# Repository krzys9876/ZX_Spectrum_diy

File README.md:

# ZX_Spectrum_diy

All boards that I designed, etched and soldered to create a full-diy replica of ZX Spectrum.
**Kicad4** (just a keyboard) and **Kicad5**

This is NOT a cycle-perfect replica so do not expect to launch fancy demos on it. 
The project started as a breadboard simplest possible computer using Z80. Quite quickly I started thinking of making a replica of ZX Spectrum - the first computer I ever used as a kid. All I wanted was to:

- launch Knight Lore - the best game ever
- write some Basic programs - to feel the magic of programming again - and I did!

Have questions? Just drop me an email.

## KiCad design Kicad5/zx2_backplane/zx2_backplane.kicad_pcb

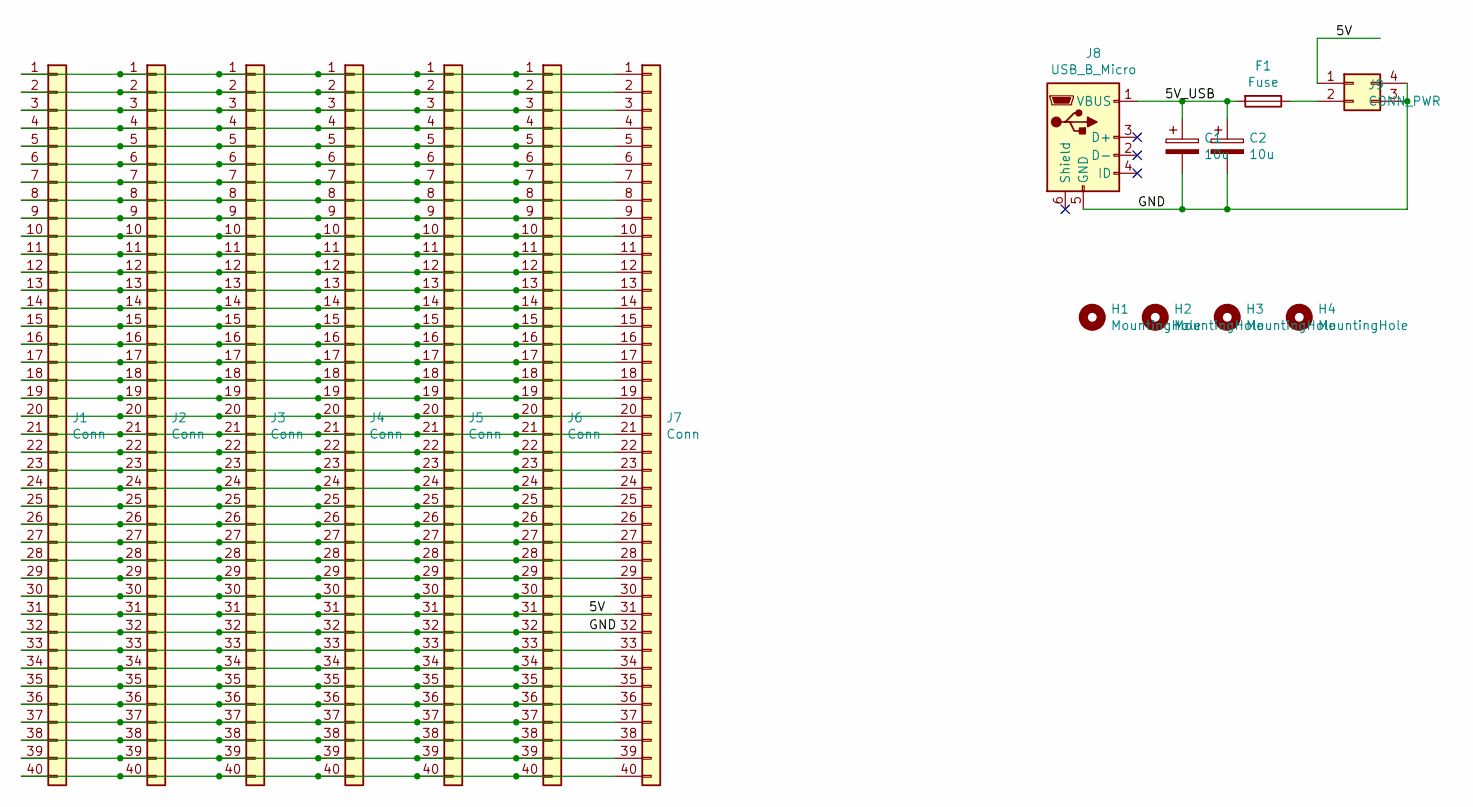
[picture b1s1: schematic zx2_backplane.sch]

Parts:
C1, C2: 10u; C_1210_3225Metric
F1: Fuse; Fuse_1812_4532Metric
H1, H2, H3, H4: MountingHole; MountingHole_3.2mm_M3
J1, J2, J3, J4, J5, J6, J7: Conn; PinHeader_1x40_P2.54mm_Vertical
J8: USB_B_Micro; USB_Micro-B_Amphenol_10104110_Horizontal
J9: CONN_PWR; PinHeader_2x02_P2.54mm_Vertical

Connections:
/5V: J1.31, J2.31, J3.31, J4.31, J5.31, J6.31, J7.31, J9.1
/5V_USB: C1.1, C2.1, F1.2, J8.1 (VBUS)
/GND: C1.2, C2.2, J1.32, J2.32, J3.32, J4.32, J5.32, J6.32, J7.32, J8.5 (GND), J9.3, J9.4
unnamed: F1.1, J9.2
unnamed: J1.1, J2.1, J3.1, J4.1, J5.1, J6.1, J7.1
unnamed: J1.2, J2.2, J3.2, J4.2, J5.2, J6.2, J7.2
unnamed: J1.3, J2.3, J3.3, J4.3, J5.3, J6.3, J7.3
unnamed: J1.4, J2.4, J3.4, J4.4, J5.4, J6.4, J7.4
unnamed: J1.5, J2.5, J3.5, J4.5, J5.5, J6.5, J7.5
unnamed: J1.6, J2.6, J3.6, J4.6, J5.6, J6.6, J7.6
unnamed: J1.7, J2.7, J3.7, J4.7, J5.7, J6.7, J7.7
unnamed: J1.8, J2.8, J3.8, J4.8, J5.8, J6.8, J7.8
unnamed: J1.9, J2.9, J3.9, J4.9, J5.9, J6.9, J7.9
unnamed: J1.10, J2.10, J3.10, J4.10, J5.10, J6.10, J7.10
unnamed: J1.11, J2.11, J3.11, J4.11, J5.11, J6.11, J7.11
unnamed: J1.12, J2.12, J3.12, J4.12, J5.12, J6.12, J7.12
unnamed: J1.13, J2.13, J3.13, J4.13, J5.13, J6.13, J7.13
unnamed: J1.14, J2.14, J3.14, J4.14, J5.14, J6.14, J7.14
unnamed: J1.15, J2.15, J3.15, J4.15, J5.15, J6.15, J7.15
unnamed: J1.16, J2.16, J3.16, J4.16, J5.16, J6.16, J7.16
unnamed: J1.17, J2.17, J3.17, J4.17, J5.17, J6.17, J7.17
unnamed: J1.18, J2.18, J3.18, J4.18, J5.18, J6.18, J7.18
unnamed: J1.19, J2.19, J3.19, J4.19, J5.19, J6.19, J7.19
unnamed: J1.20, J2.20, J3.20, J4.20, J5.20, J6.20, J7.20
unnamed: J1.21, J2.21, J3.21, J4.21, J5.21, J6.21, J7.21
unnamed: J1.22, J2.22, J3.22, J4.22, J5.22, J6.22, J7.22
unnamed: J1.23, J2.23, J3.23, J4.23, J5.23, J6.23, J7.23
unnamed: J1.24, J2.24, J3.24, J4.24, J5.24, J6.24, J7.24
unnamed: J1.25, J2.25, J3.25, J4.25, J5.25, J6.25, J7.25
unnamed: J1.26, J2.26, J3.26, J4.26, J5.26, J6.26, J7.26
unnamed: J1.27, J2.27, J3.27, J4.27, J5.27, J6.27, J7.27
unnamed: J1.28, J2.28, J3.28, J4.28, J5.28, J6.28, J7.28
unnamed: J1.29, J2.29, J3.29, J4.29, J5.29, J6.29, J7.29
unnamed: J1.30, J2.30, J3.30, J4.30, J5.30, J6.30, J7.30
unnamed: J1.33, J2.33, J3.33, J4.33, J5.33, J6.33, J7.33
unnamed: J1.34, J2.34, J3.34, J4.34, J5.34, J6.34, J7.34
unnamed: J1.35, J2.35, J3.35, J4.35, J5.35, J6.35, J7.35
unnamed: J1.36, J2.36, J3.36, J4.36, J5.36, J6.36, J7.36
unnamed: J1.37, J2.37, J3.37, J4.37, J5.37, J6.37, J7.37
unnamed: J1.38, J2.38, J3.38, J4.38, J5.38, J6.38, J7.38
unnamed: J1.39, J2.39, J3.39, J4.39, J5.39, J6.39, J7.39
unnamed: J1.40, J2.40, J3.40, J4.40, J5.40, J6.40, J7.40

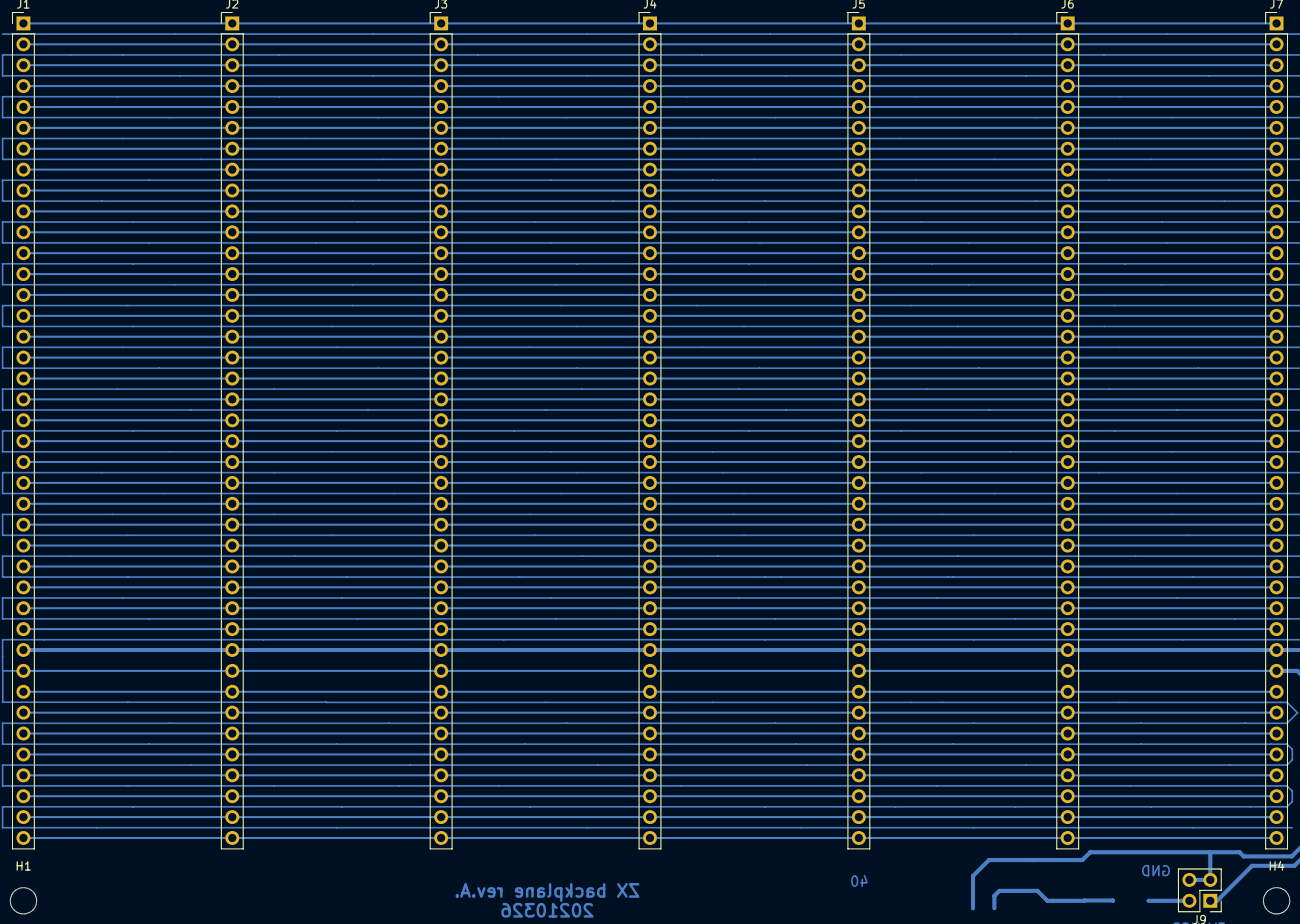
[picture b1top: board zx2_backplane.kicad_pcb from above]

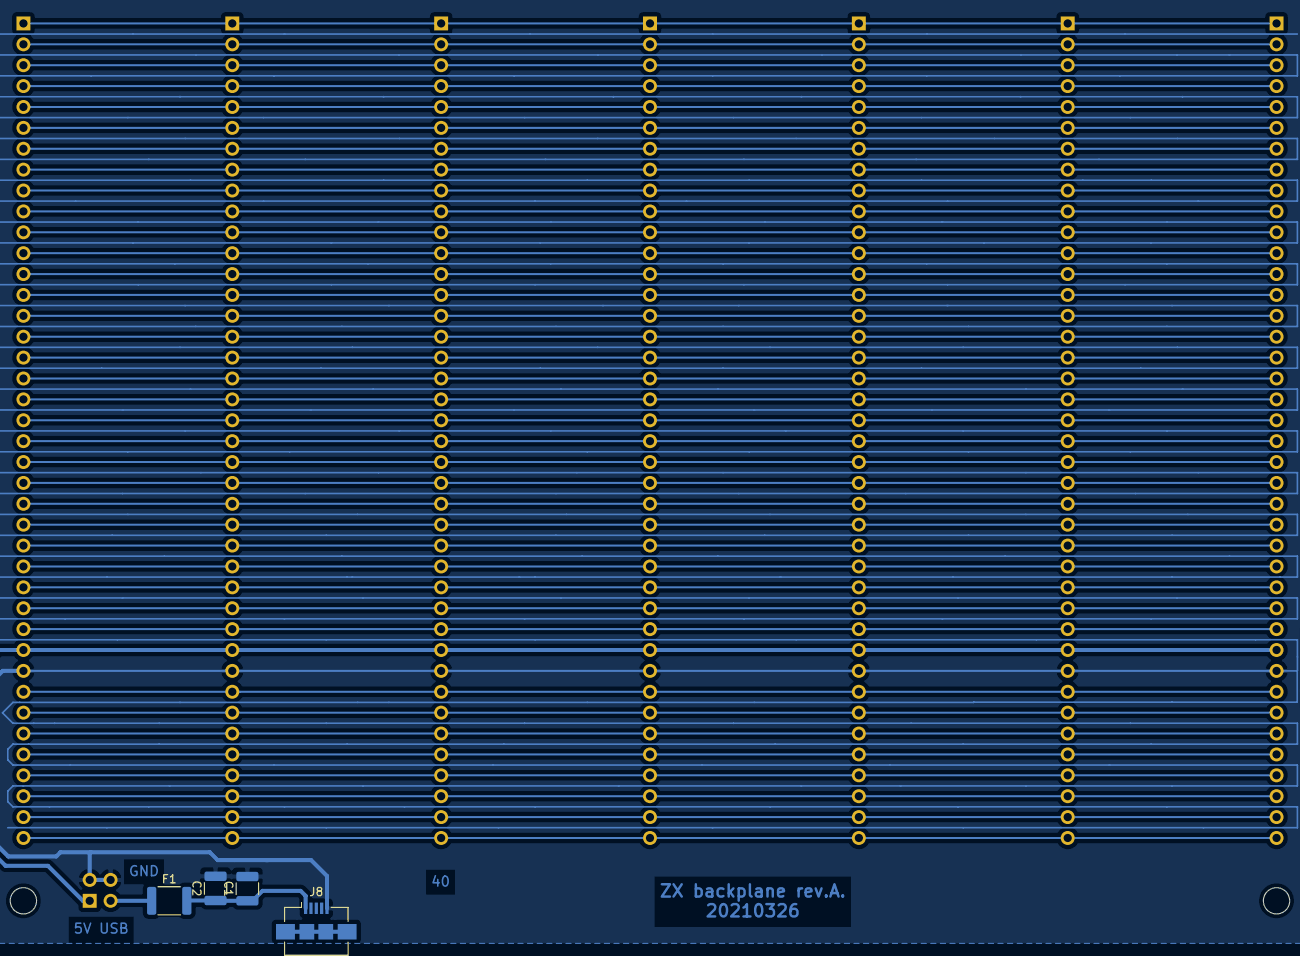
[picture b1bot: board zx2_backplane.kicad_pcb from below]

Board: 2 copper layers, 16 parts (4 on the bottom side), 42 nets.

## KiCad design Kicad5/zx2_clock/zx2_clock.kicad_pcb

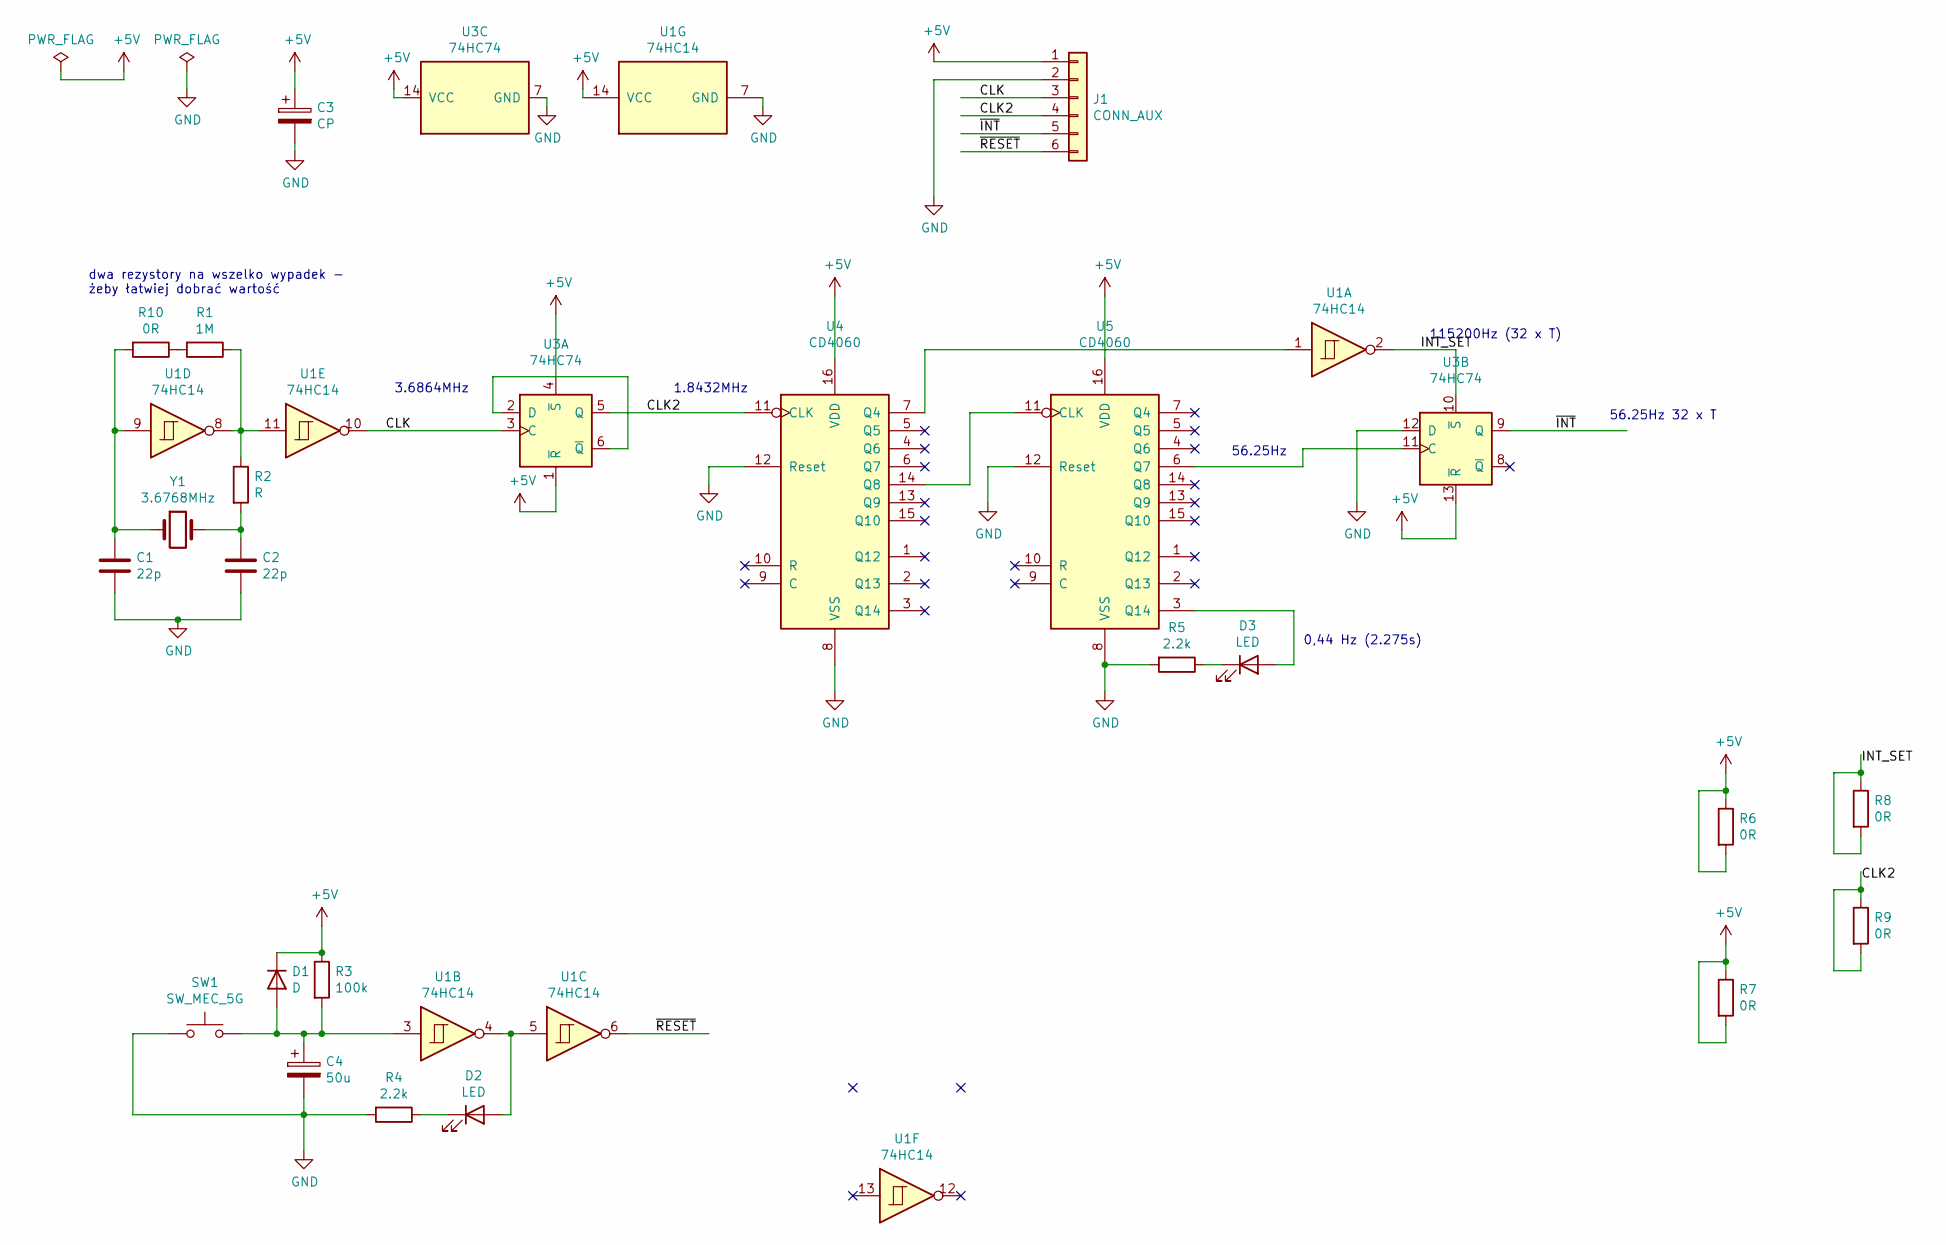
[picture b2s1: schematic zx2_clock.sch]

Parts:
C1, C2: 22p; C_0603_1608Metric
C3: CP; C_1210_3225Metric
C4: 50u; CP_Elec_5x3
D1: D; C_0805_2012Metric
D2, D3: LED; C_0805_2012Metric
J1: CONN_AUX; PinHeader_1x06_P2.54mm_Horizontal
R1: 1M; C_0805_2012Metric
R2: R; C_0805_2012Metric
R3: 100k; C_0805_2012Metric
R4, R5: 2.2k; C_0805_2012Metric
R6, R7, R8, R9: 0R; R_1206_3216Metric
R10: 0R; C_0805_2012Metric
SW1: SW_MEC_5G; SW_SPST_EVQPE1
U1: 74HC14; DIP-14_W7.62mm
U3: 74HC74; DIP-14_W7.62mm
U4, U5: CD4060; DIP-16_W7.62mm
Y1: 3.6768MHz; Crystal_SMD_HC49-SD

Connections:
+5V: C3.1, D1.1 (K), J1.1, R3.1, R6.1, R6.2, R7.1, R7.2, U1.14 (VCC), U3.1 (~R), U3.4 (~S), U3.13 (~R), U3.14 (VCC), U4.16 (VDD), U5.16 (VDD)
/CLK: J1.3, U1.10, U3.3 (C)
/CLK2: J1.4, R9.1, R9.2, U3.5 (Q), U4.11 (CLK)
/INT_SET: R8.1, R8.2, U1.2, U3.10 (~S)
/~INT: J1.5, U3.9 (Q)
/~RESET: J1.6, U1.6
GND: C1.2, C2.2, C3.2, C4.2, J1.2, R4.2, R5.2, SW1.1, U1.7 (GND), U3.7 (GND), U3.12 (D), U4.8 (VSS), U4.12 (Reset), U5.8 (VSS), U5.12 (Reset)
unnamed: C1.1, R10.2, U1.9, Y1.1
unnamed: C2.1, R2.2, Y1.2
unnamed: C4.1, D1.2 (A), R3.2, SW1.2, U1.3
unnamed: D2.1 (K), R4.1
unnamed: D2.2 (A), U1.4, U1.5
unnamed: D3.1 (K), R5.1
unnamed: D3.2 (A), U5.3 (Q14)
unnamed: R1.1, R2.1, U1.8, U1.11
unnamed: R1.2, R10.1
unnamed: U1.1, U4.7 (Q4)
unnamed: U3.2 (D), U3.6 (~Q)
unnamed: U3.11 (C), U5.6 (Q7)
unnamed: U4.14 (Q8), U5.11 (CLK)

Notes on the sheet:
56.25Hz
115200Hz (32 x T)
3.6864MHz
1.8432MHz
56.25Hz 32 x T
0,44 Hz (2.275s)
dwa rezystory na wszelko wypadek - żeby łatwiej dobrać wartość

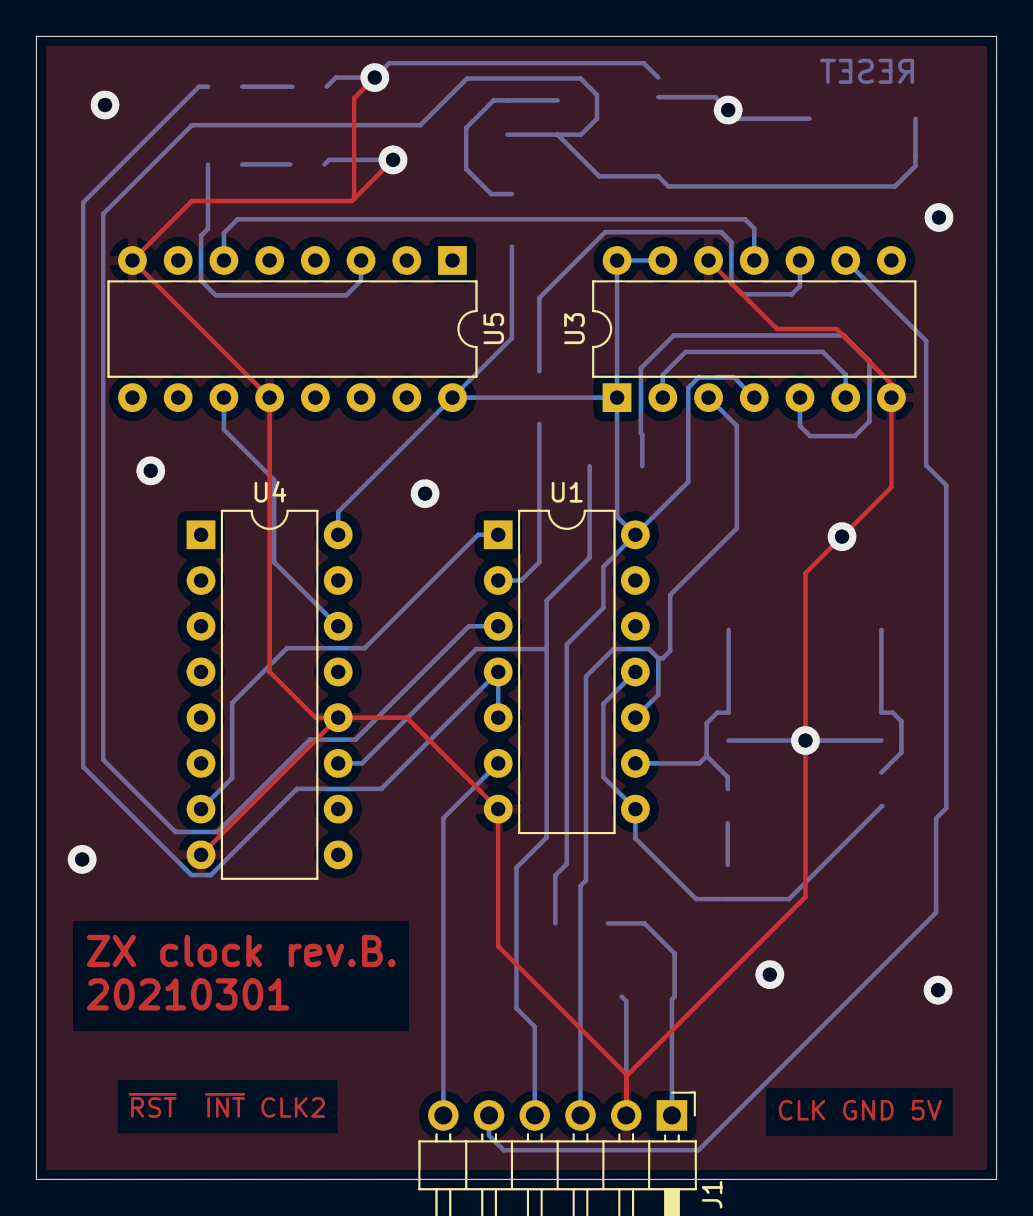
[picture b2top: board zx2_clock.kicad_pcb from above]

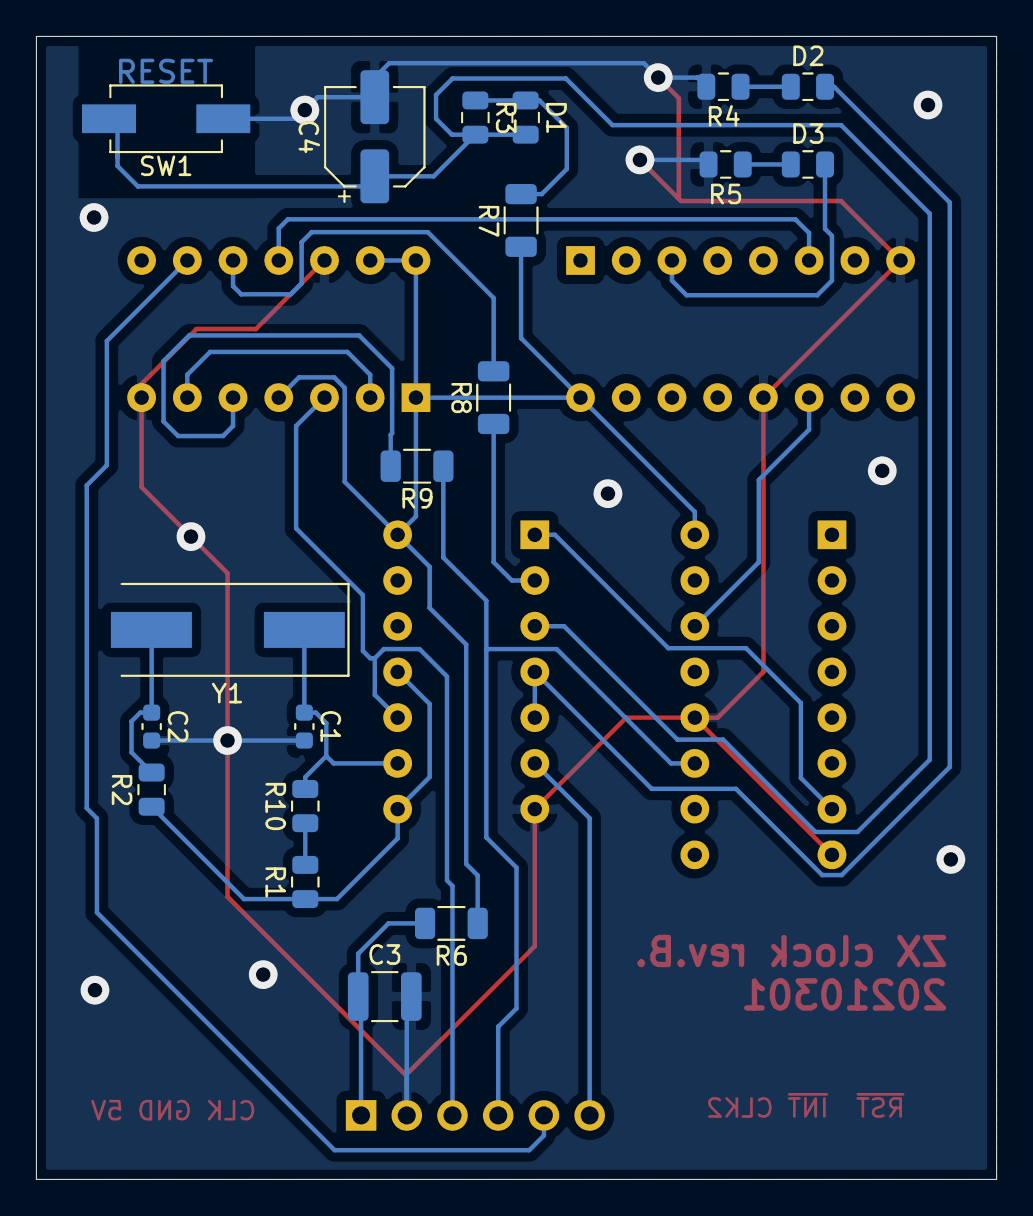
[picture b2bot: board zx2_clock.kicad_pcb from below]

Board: 2 copper layers, 53.3 x 63.5 mm, 24 parts (19 on the bottom side), 20 nets.

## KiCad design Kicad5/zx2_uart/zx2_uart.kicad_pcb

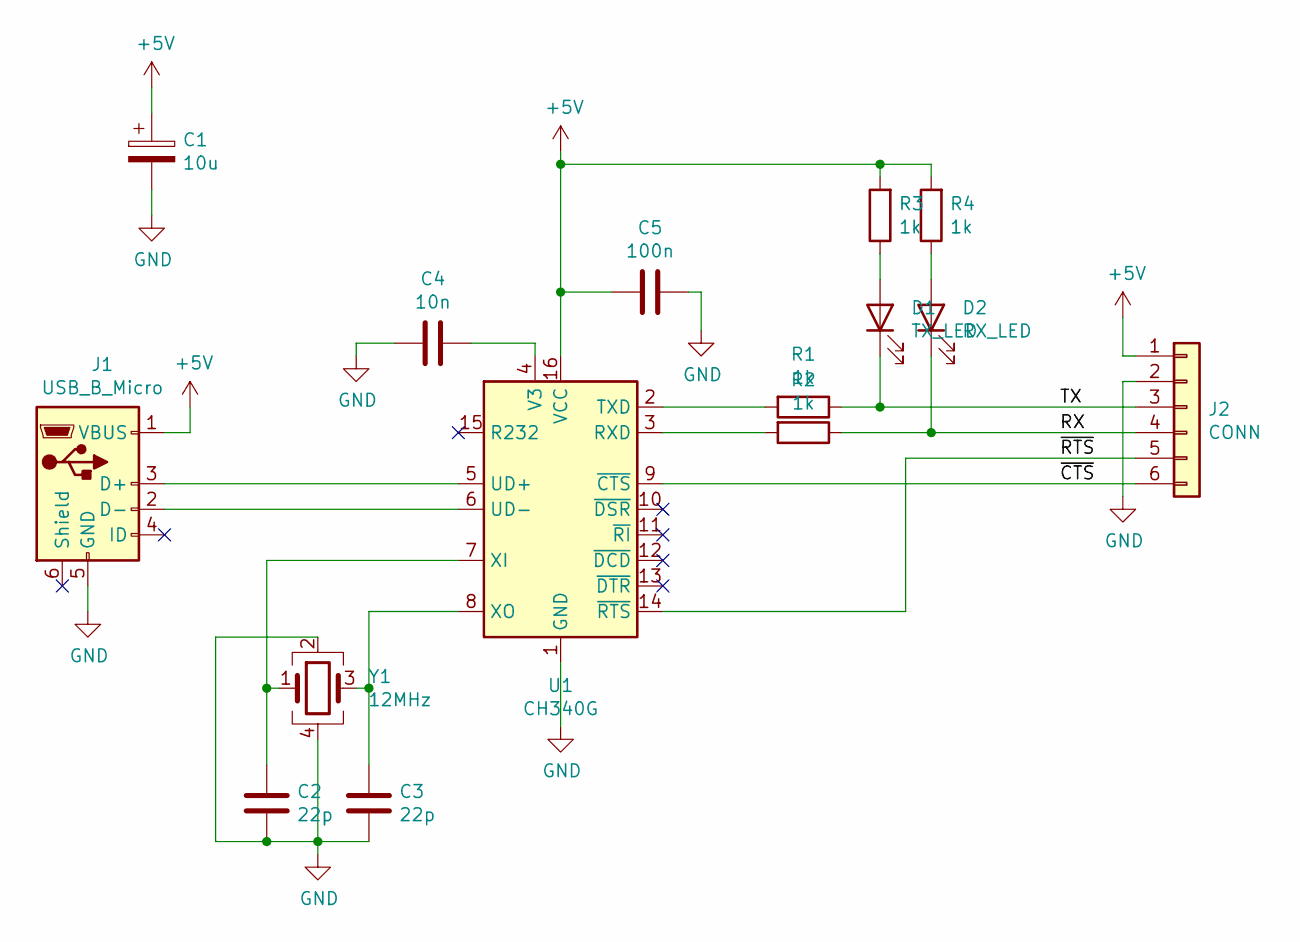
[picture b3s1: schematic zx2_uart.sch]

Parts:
C1: 10u; C_1210_3225Metric
C2, C3: 22p; C_0603_1608Metric
C4: 10n; C_1206_3216Metric
C5: 100n; C_1206_3216Metric
D1: TX_LED; D_0805_2012Metric
D2: RX_LED; D_0805_2012Metric
J1: USB_B_Micro; USB_Micro-B_Amphenol_10104110_Horizontal
J2: CONN; PinHeader_1x06_P2.54mm_Vertical
R1, R2, R3, R4: 1k; R_0805_2012Metric
U1: CH340G; SOIC-16_3.9x9.9mm_P1.27mm
Y1: 12MHz; Crystal_SMD_3225-4Pin_3.2x2.5mm

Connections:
+5V: C1.1, C5.2, J1.1 (VBUS), J2.1, R3.2, R4.2, U1.16 (VCC)
/RX: D2.1 (K), J2.4, R2.1
/TX: D1.1 (K), J2.3, R1.1
/~CTS: J2.6, U1.9 (~CTS)
/~RTS: J2.5, U1.14 (~RTS)
GND: C1.2, C2.1, C3.1, C4.2, C5.1, J1.5 (GND), J2.2, U1.1 (GND), Y1.2, Y1.4
unnamed: C2.2, U1.7 (XI), Y1.1
unnamed: C3.2, U1.8 (XO), Y1.3
unnamed: C4.1, U1.4 (V3)
unnamed: D1.2 (A), R3.1
unnamed: D2.2 (A), R4.1
unnamed: J1.2 (D-), U1.6 (UD-)
unnamed: J1.3 (D+), U1.5 (UD+)
unnamed: R1.2, U1.2 (TXD)
unnamed: R2.2, U1.3 (RXD)

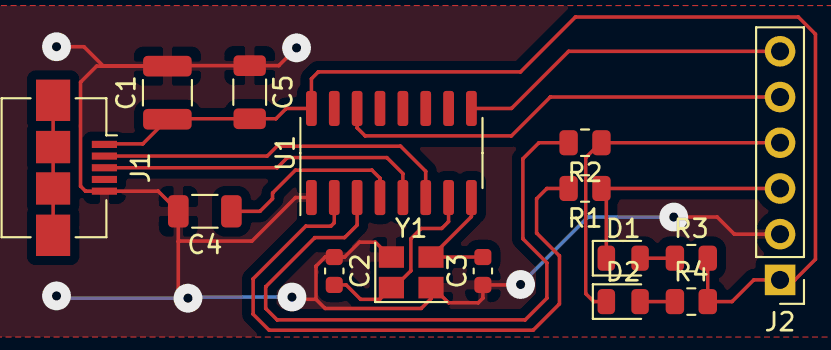
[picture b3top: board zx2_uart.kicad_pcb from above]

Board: 2 copper layers, 15 parts (0 on the bottom side), 15 nets.

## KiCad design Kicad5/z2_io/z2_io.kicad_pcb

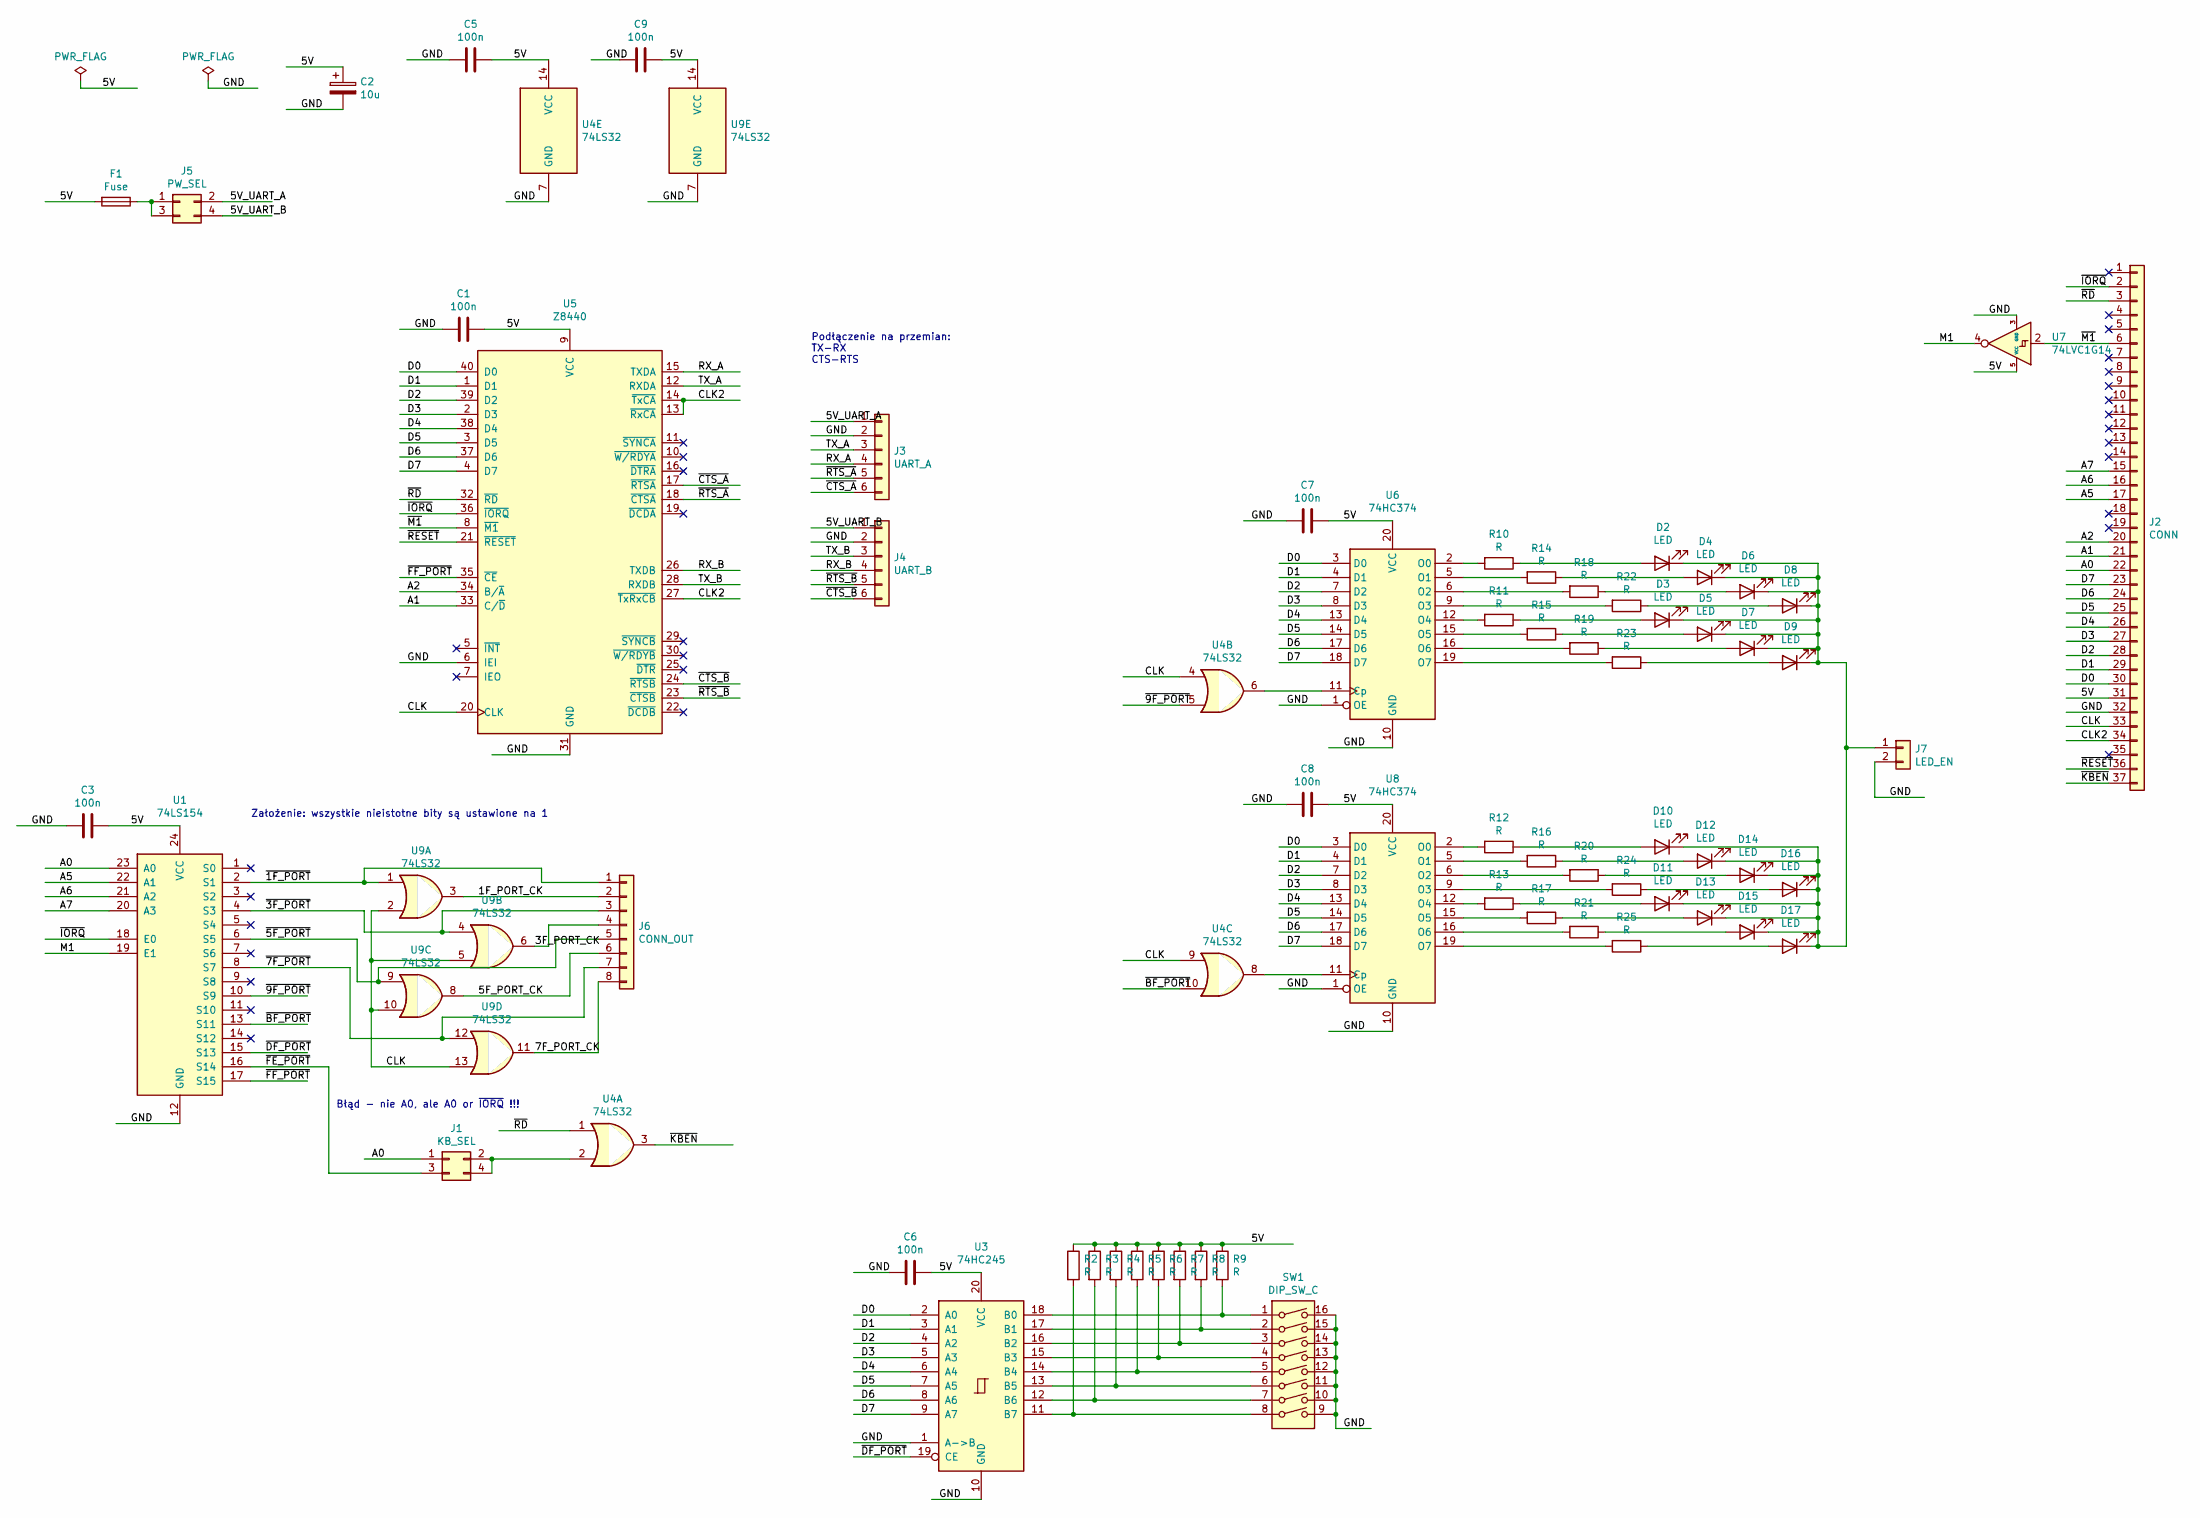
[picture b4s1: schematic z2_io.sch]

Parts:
C1, C3, C5, C6, C7, C8, C9: 100n; C_1206_3216Metric
C2: 10u; C_1210_3225Metric
D2, D3, D4, D5, D6, D7, D8, D9, D10, D11, D12, D13, D14, D15, D16, D17: LED; D_0805_2012Metric
F1: Fuse; Fuse_1812_4532Metric
J1: KB_SEL; PinHeader_2x02_P2.54mm_Vertical
J2: CONN; PinHeader_1x37_P2.54mm_Horizontal
J3: UART_A; PinHeader_1x06_P2.54mm_Horizontal
J4: UART_B; PinHeader_1x06_P2.54mm_Horizontal
J5: PW_SEL; PinHeader_2x02_P2.54mm_Vertical
J6: CONN_OUT; PinHeader_2x04_P2.54mm_Vertical
J7: LED_EN; PinHeader_1x02_P2.54mm_Vertical
R2, R3, R4, R5, R6, R7, R8, R9, R10, R11, R12, R13, R14, R15, R16, R17, R18, R19, R20, R21, R22, R23, R24, R25: R; R_0805_2012Metric
SW1: DIP_SW_C; DIP-16_W7.62mm
U1: 74LS154; DIP-24_W7.62mm
U3: 74HC245; DIP-20_W7.62mm
U4, U9: 74LS32; DIP-14_W7.62mm
U5: Z8440; DIP-40_W15.24mm
U6, U8: 74HC374; DIP-20_W7.62mm
U7: 74LVC1G14; SOT-353_SC-70-5

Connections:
/1F_PORT_CK: J6.2, U9.3
/3F_PORT_CK: J6.4, U9.6
/5F_PORT_CK: J6.6, U9.8
/5V: C1.1, C2.1, C3.1, C5.1, C6.1, C7.1, C8.1, C9.1, F1.2, J2.31, R2.1, R3.1, R4.1, R5.1, R6.1, R7.1, R8.1, R9.1, U1.24 (VCC), U3.20 (VCC), U4.14 (VCC), U5.9 (VCC), U6.20 (VCC), U7.5 (VCC), U8.20 (VCC), U9.14 (VCC)
/5V_UART_A: J3.1, J5.2
/5V_UART_B: J4.1, J5.4
/7F_PORT_CK: J6.8, U9.11
/A0: J1.1, J2.22, U1.23 (A0)
/A1: J2.21, U5.33 (C/~D)
/A2: J2.20, U5.34 (B/~A)
/A5: J2.17, U1.22 (A1)
/A6: J2.16, U1.21 (A2)
/A7: J2.15, U1.20 (A3)
/CLK: J2.33, U4.4, U4.9, U5.20 (CLK), U9.2, U9.5, U9.10, U9.13
/CLK2: J2.34, U5.13 (~RxCA), U5.14 (~TxCA), U5.27 (~TxRxCB)
/D0: J2.30, U3.2 (A0), U5.40 (D0), U6.3 (D0), U8.3 (D0)
/D1: J2.29, U3.3 (A1), U5.1 (D1), U6.4 (D1), U8.4 (D1)
/D2: J2.28, U3.4 (A2), U5.39 (D2), U6.7 (D2), U8.7 (D2)
/D3: J2.27, U3.5 (A3), U5.2 (D3), U6.8 (D3), U8.8 (D3)
/D4: J2.26, U3.6 (A4), U5.38 (D4), U6.13 (D4), U8.13 (D4)
/D5: J2.25, U3.7 (A5), U5.3 (D5), U6.14 (D5), U8.14 (D5)
/D6: J2.24, U3.8 (A6), U5.37 (D6), U6.17 (D6), U8.17 (D6)
/D7: J2.23, U3.9 (A7), U5.4 (D7), U6.18 (D7), U8.18 (D7)
/GND: C1.2, C2.2, C3.2, C5.2, C6.2, C7.2, C8.2, C9.2, J2.32, J3.2, J4.2, J7.2, SW1.9, SW1.10, SW1.11, SW1.12, SW1.13, SW1.14, SW1.15, SW1.16, U1.12 (GND), U3.1 (A->B), U3.10 (GND), U4.7 (GND), U5.6 (IEI), U5.31 (GND), U6.1 (OE), U6.10 (GND), U7.3 (GND), U8.1 (OE), U8.10 (GND), U9.7 (GND)
/M1: U1.19 (E1), U7.4
/RX_A: J3.4, U5.15 (TXDA)
/RX_B: J4.4, U5.26 (TXDB)
/TX_A: J3.3, U5.12 (RXDA)
/TX_B: J4.3, U5.28 (RXDB)
/~1F_PORT: J6.1, U1.2 (S1), U9.1
/~3F_PORT: J6.3, U1.4 (S3), U9.4
/~5F_PORT: J6.5, U1.6 (S5), U9.9
/~7F_PORT: J6.7, U1.8 (S7), U9.12
/~9F_PORT: U1.10 (S9), U4.5
/~BF_PORT: U1.13 (S11), U4.10
/~CTS_A: J3.6, U5.17 (~RTSA)
/~CTS_B: J4.6, U5.24 (~RTSB)
/~DF_PORT: U1.15 (S13), U3.19 (CE)
/~FE_PORT: J1.3, U1.16 (S14)
/~FF_PORT: U1.17 (S15), U5.35 (~CE)
/~IORQ: J2.2, U1.18 (E0), U5.36 (~IORQ)
/~KBEN: J2.37, U4.3
/~M1: J2.6, U5.8 (~M1), U7.2
/~RD: J2.3, U4.1, U5.32 (~RD)
/~RESET: J2.36, U5.21 (~RESET)
/~RTS_A: J3.5, U5.18 (~CTSA)
/~RTS_B: J4.5, U5.23 (~CTSB)
unnamed: D2.2 (A), R10.1
unnamed: D3.2 (A), R11.1
unnamed: D4.2 (A), R14.1
unnamed: D5.2 (A), R15.1
unnamed: D6.2 (A), R18.1
unnamed: D7.2 (A), R19.1
unnamed: D8.2 (A), R22.1
unnamed: D9.2 (A), R23.1
unnamed: D2.1 (K), D3.1 (K), D4.1 (K), D5.1 (K), D6.1 (K), D7.1 (K), D8.1 (K), D9.1 (K), D10.1 (K), D11.1 (K), D12.1 (K), D13.1 (K), D14.1 (K), D15.1 (K), D16.1 (K), D17.1 (K), J7.1
unnamed: D10.2 (A), R12.1
unnamed: D11.2 (A), R13.1
unnamed: D12.2 (A), R16.1
unnamed: D13.2 (A), R17.1
unnamed: D14.2 (A), R20.1
unnamed: D15.2 (A), R21.1
unnamed: D16.2 (A), R24.1
unnamed: D17.2 (A), R25.1
unnamed: F1.1, J5.1, J5.3
unnamed: J1.2, J1.4, U4.2
unnamed: R2.2, SW1.8, U3.11 (B7)
unnamed: R3.2, SW1.7, U3.12 (B6)
unnamed: R4.2, SW1.6, U3.13 (B5)
unnamed: R5.2, SW1.5, U3.14 (B4)
unnamed: R6.2, SW1.4, U3.15 (B3)
unnamed: R7.2, SW1.3, U3.16 (B2)
unnamed: R8.2, SW1.2, U3.17 (B1)
unnamed: R9.2, SW1.1, U3.18 (B0)
unnamed: R10.2, U6.2 (O0)
unnamed: R11.2, U6.12 (O4)
unnamed: R12.2, U8.2 (O0)
unnamed: R13.2, U8.12 (O4)
unnamed: R14.2, U6.5 (O1)
unnamed: R15.2, U6.15 (O5)
unnamed: R16.2, U8.5 (O1)
unnamed: R17.2, U8.15 (O5)
unnamed: R18.2, U6.6 (O2)
unnamed: R19.2, U6.16 (O6)
unnamed: R20.2, U8.6 (O2)
unnamed: R21.2, U8.16 (O6)
unnamed: R22.2, U6.9 (O3)
unnamed: R23.2, U6.19 (O7)
unnamed: R24.2, U8.9 (O3)
unnamed: R25.2, U8.19 (O7)
unnamed: U4.6, U6.11 (Cp)
unnamed: U4.8, U8.11 (Cp)

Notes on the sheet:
Podłączenie na przemian: TX-RX CTS-RTS
Założenie: wszystkie nieistotne bity są ustawione na 1
Błąd - nie A0, ale A0 or ~IORQ~ !!!

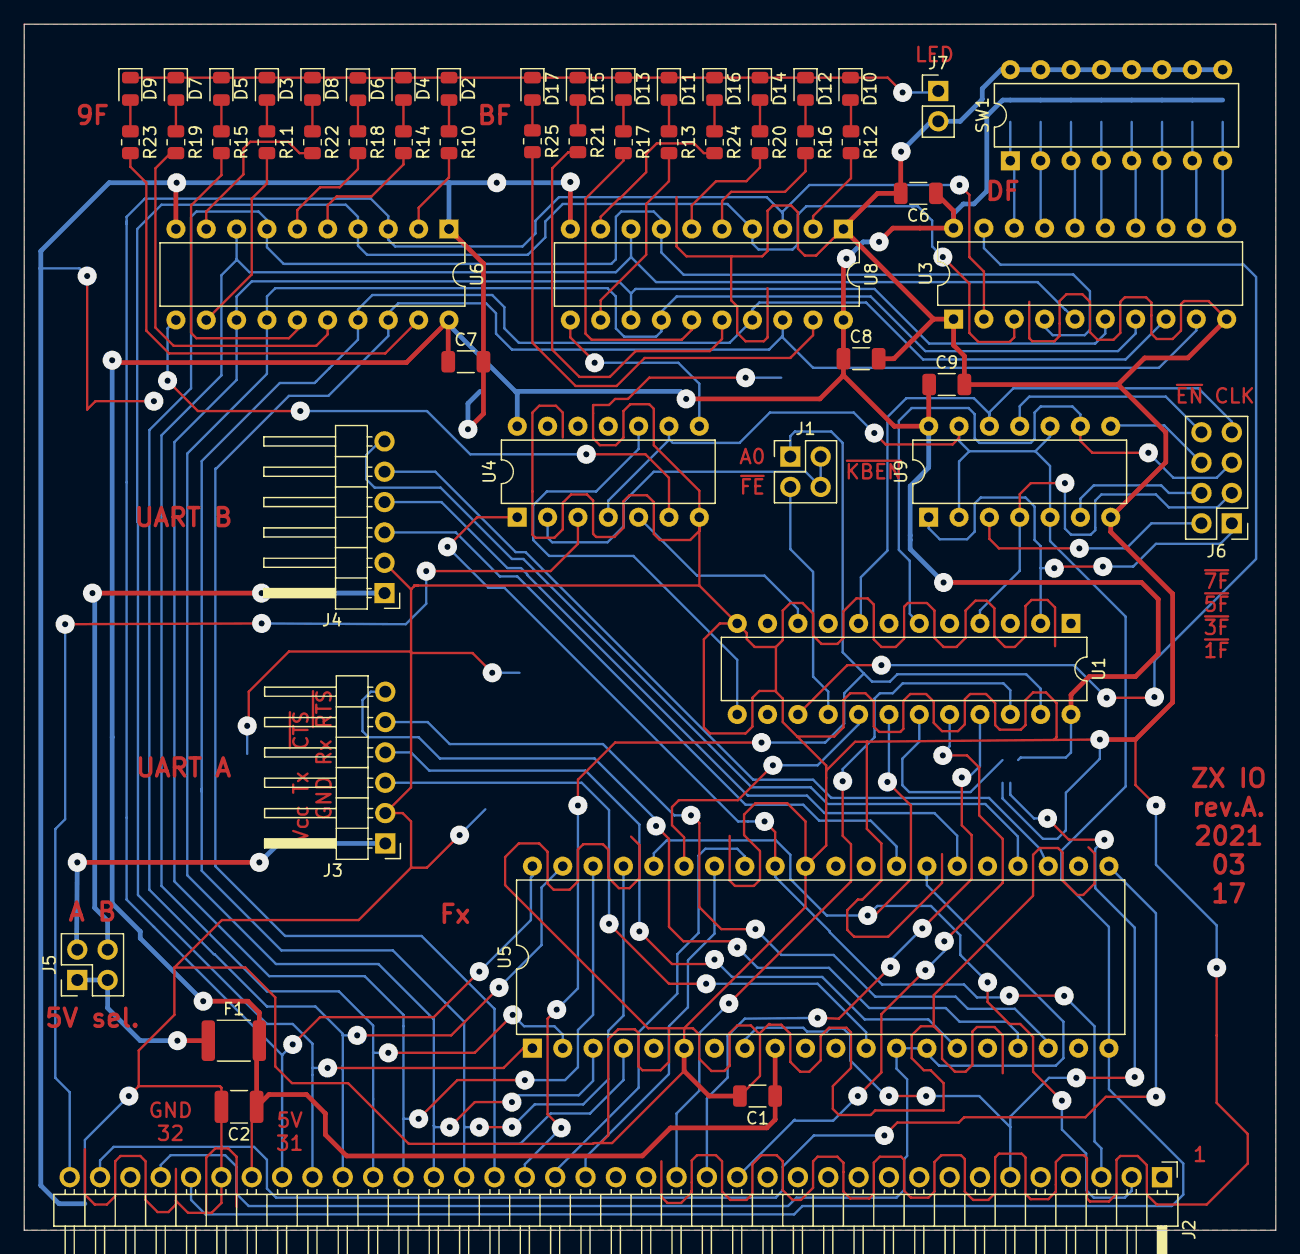
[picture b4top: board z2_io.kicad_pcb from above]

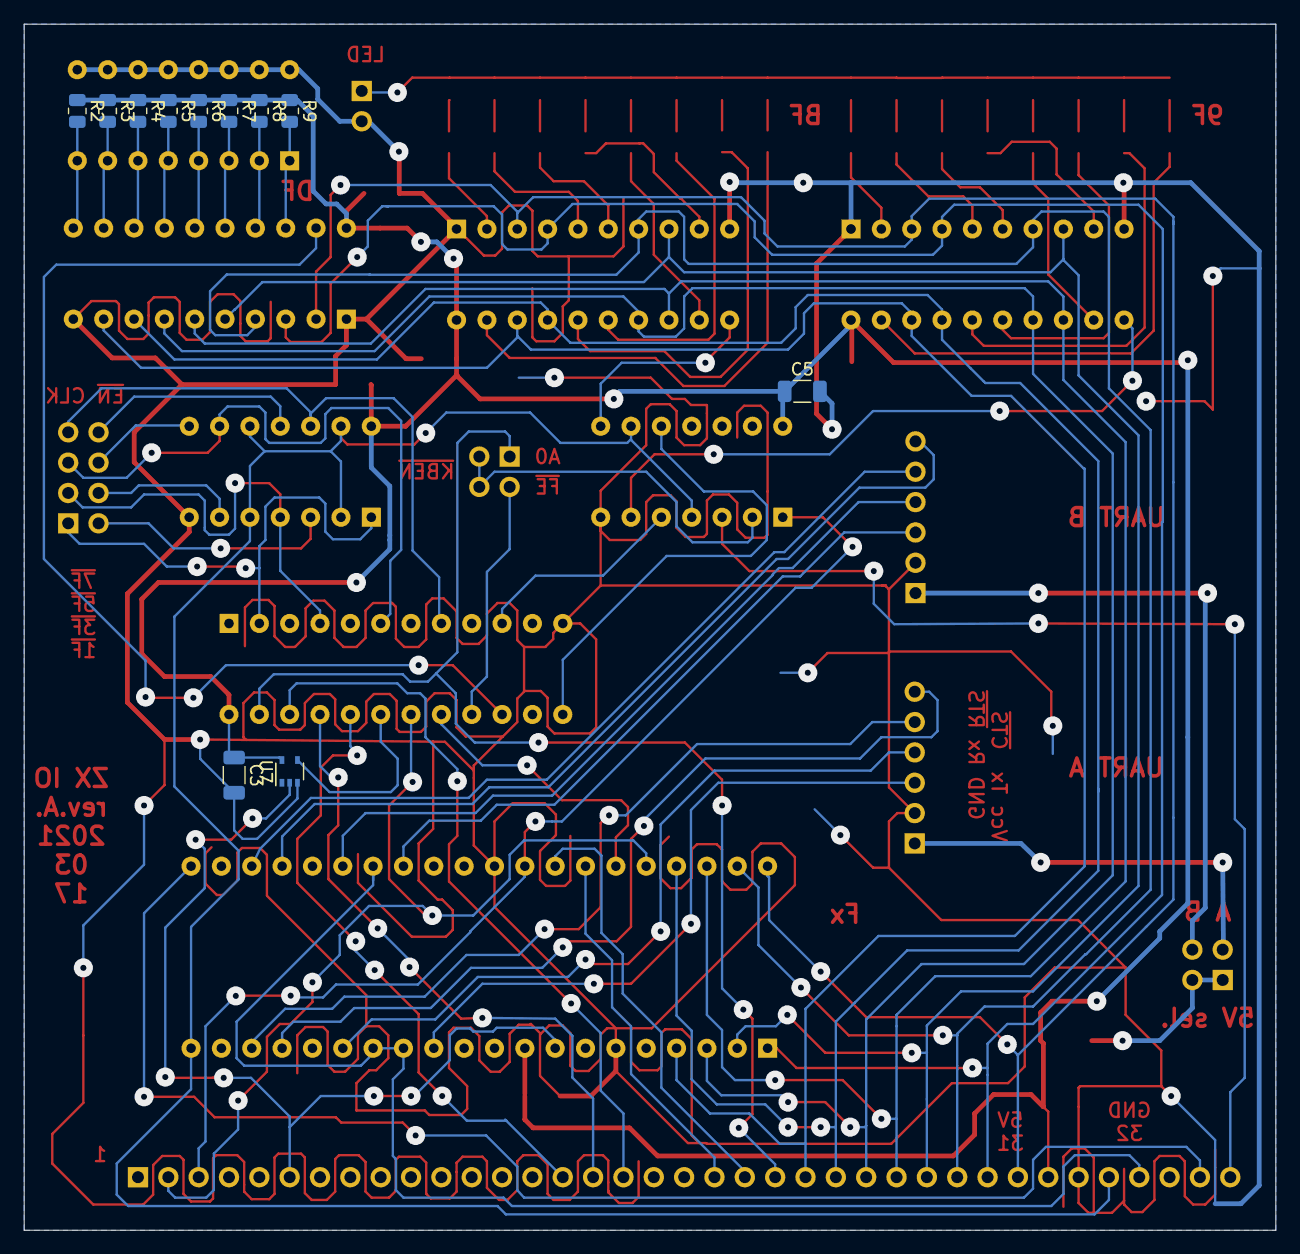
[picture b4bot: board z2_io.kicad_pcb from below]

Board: 2 copper layers, 104.8 x 101.0 mm, 65 parts (11 on the bottom side), 92 nets.
